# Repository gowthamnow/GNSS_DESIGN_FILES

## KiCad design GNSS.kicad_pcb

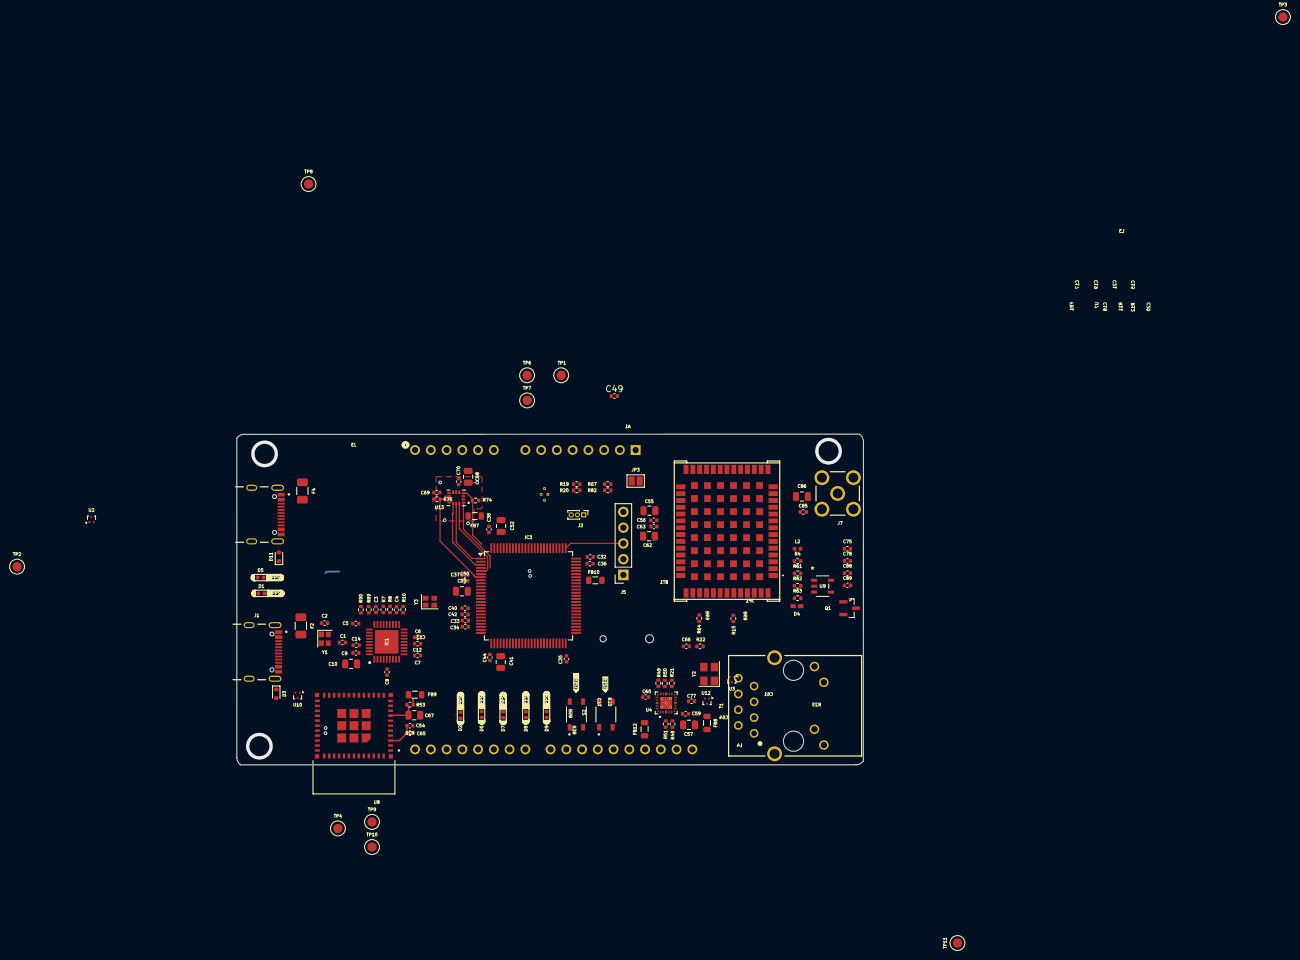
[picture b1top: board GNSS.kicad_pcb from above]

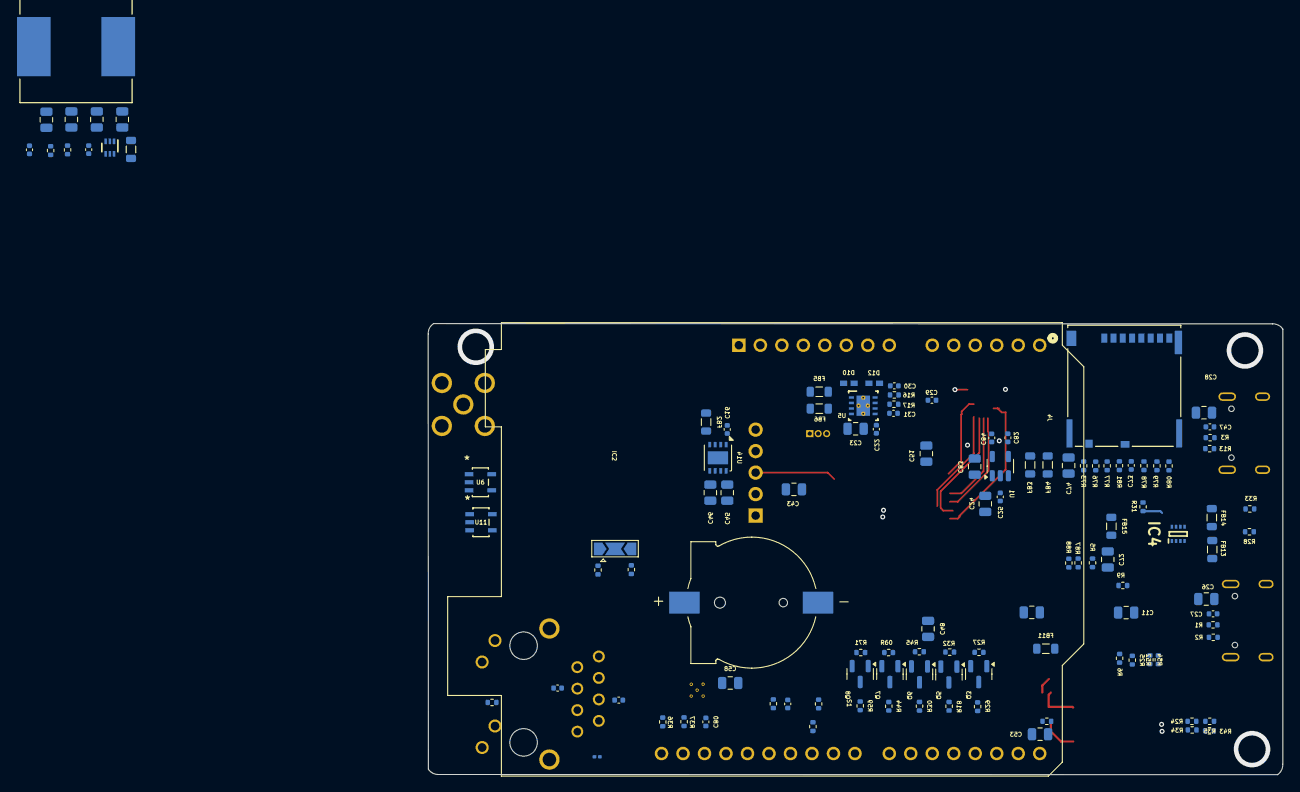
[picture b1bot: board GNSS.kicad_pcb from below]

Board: 4 copper layers, 101.0 x 53.3 mm, 240 parts (116 on the bottom side), 175 nets.

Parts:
A1: Arduino_UNO_R3
BT1: 1056; BAT_1056
C1, C2, C42, C44: 18p; C_0402_1005Metric
C3, C4, C5, C6, C7, C8, C9, C12, C14, C16, C25, C49, C54, C65, C71, C84: 0.1u; C_0402_1005Metric
C10, C23, C43: 4u7; C_0805_2012Metric
C11, C13, C26, C28, C39, C41, C48, C55, C57, C58, C67, C72: 1u; C_0805_2012Metric
C15: 4u7/25V; C_0805_2012Metric
C17, C19, C21: 22u/25V; C_0805_2012Metric
C18, C20: 0.1u/25V; C_0402_1005Metric
C22, C27, C32, C33, C34, C35, C36, C37, C38, C40, C47, C50, C56, C59, C60, C63, C68, C73, C78, C80, C85, C89: 100n; C_0402_1005Metric
C24, C45, C46, C53, C62, C74: 10u; C_0805_2012Metric
C29: 4n7; C_0402_1005Metric
C30, C31: 100p; C_0402_1005Metric
C51, C52: 2.2u; C_0805_2012Metric
C61, C64, C69, C88: 10n; C_0402_1005Metric
C66, C77: 20p; C_0402_1005Metric
C70, C83, C86: 2u2; C_0805_2012Metric
C75: 47p; C_0402_1005Metric
C82: 470p; C_0402_1005Metric
D1, D2, D5, D6, D7, D8, D9: SML-P12U2TT86R; LED_0402_1005Metric
D3, D11: ESD5V0D5-TP; D_SOD-523
D4, D10, D12: PESD0402-140; DIO_PESD0402-140
F2, F4: MF-NSMF150-2; Fuse_1206_3216Metric
FB1, FB2, FB3, FB4, FB5, FB6, FB7, FB8, FB9, FB10, FB11, FB12, FB13, FB14, FB15: FerriteBead; L_0805_2012Metric
IC1: USB2513B_M2; QFN50P600X600X100-37N-D
IC2: ZED-F9P-05B; ZEDF9P05B
IC3: STM32H563VGTx; LQFP-100_14x14mm_P0.5mm
IC4: LM66200DRLR; SOTFL50P160X60-8N
J1, J4: USB4105-GF-A-120; GCT_USB4105-GF-A-120
J2: Conn; PinHeader_1x03_P1.00mm_Vertical
J3: 5033981892; CONN_503398-1892_MOL
J5: Conn_01x05_Pin; PinSocket_1x05_P2.54mm_Vertical
J7: SMA-J-P-X-RA-TH1; SAMTEC_SMA-J-P-X-RA-TH1
JP1: SolderJumper_3_Open; SolderJumper-3_P2.0mm_Open_TrianglePad1.0x1.5mm
JP3: SolderJumper_2_Open; SolderJumper-2_P1.3mm_Open_Pad1.0x1.5mm
L2: LQG15HS47NJ02D; L_0402_1005Metric
L3: SRR1208-120ML; IND_BOURNS_SRR1208
L4: WE-CBF_0603; R_0201_0603Metric
Q1: PMOS; SOT103P240X110-3N
Q3, Q5, Q6, Q7, Q8: BC849; SOT-23
R1, R2, R3, R13: 5K1; R_0402_1005Metric
R4, R5, R7, R12, R63, R87, R88, R89, R90: 100K; R_0402_1005Metric
R6: 12K; R_0402_1005Metric
R8, R9, R10, R15, R25, R26, R27, R31, R32, R35, R38, R43, R45, R48, R51, R52, R53, R54, R58, R60, R64, R67, R68, R69, R70, R71, R73, R74, R75, R76, R77, R78, R79, R80, R81, R82: 10K; R_0402_1005Metric
R11: 450K; R_0402_1005Metric
R16, R17: 60E; R_0402_1005Metric
R18, R28, R29, R30, R33, R44, R59: 560E; R_0402_1005Metric
R19, R20: 0E; R_0402_1005Metric
R21: 6K49; R_0402_1005Metric
R22: 1M; R_0402_1005Metric
R23: 470R; R_0402_1005Metric
R24, R34: 22E; R_0402_1005Metric
R36, R37: 4K7; R_0402_1005Metric
R49, R50: 2K2; R_0402_1005Metric
R61: 30E; R_0402_1005Metric
R62: 1K; R_0402_1005Metric
S1, S2: SKRPABE010; SW_SKRPABE010
T1: WE-RJ45_7499010211A; 7499010211A
TP1, TP2, TP3, TP4, TP6, TP7, TP8, TP9, TP10, TP11: TestPoint; TestPoint_Pad_D2.0mm
U1: MIC5205-3.3YM5; SOT-23-5
U2, U3, U10, U12: TPD2EUSB30A; Texas_DRT-3
U4: DP83825IRMQR; XCVR_DP83825IRMQR
U5: TCAN1042VDRBRQ1; DRB0008F
U6, U11: NC7SZ125M5X; SC-74A_318BQ_ONS
U7: TLV62569ADRLR; DRL0006A
U8: ESP32-C3-MINI-1-N4; XCVR_ESP32-C3-MINI-1-N4
U9: TLV3201AIDBVR; DBV5_TEX
U13: ICM-42688-P; PQFN50P300X250X97-14N
U14: NCV8705ML33TCG; DFN-8-1EP_3x3mm_P0.65mm_EP1.55x2.4mm
Y1, Y3: MURATA_XRCGB24M000FFS1DR0; Crystal_SMD_2016-4Pin_2.0x1.6mm
Y2: ECS-250-18-33-JGN-TR; Crystal_SMD_3225-4Pin_3.2x2.5mm

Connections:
5V: C15.2, C18.2, C19.1, FB1.2, U7.3 (VIN), U7.5 (EN)
+3V3: C17.1, C20.2, C21.1, FB4.1, FB6.1, FB8.1, FB9.1, FB10.1, FB11.1, FB12.1, L3.1, R9.2, R11.2, R36.2, R37.2, R38.2, TP3.1 (1_1)
+3V3_ARDUINO: A1.4 (3V3), FB12.2
+3V3_CAN: FB6.2, U5.5 (VIO)
+3V3_ESP: C53.1, C54.2, C65.2, FB9.2, R25.1, R26.1, R35.2, R43.2, R52.2, R53.2, R54.1, U8.3 (3V3)
+3V3_ETH: C57.1, C58.1, C59.2, C60.2, FB8.2, R48.1, R49.1, R50.1, R51.1, T1.9, U4.6 (VDDA3V3), U4.19 (VDDIO)
+3V3_GNSS: C45.2, C49.2, C55.1, C56.2, C62.1, C63.2, IC2.33 (VCC_1), IC2.34 (VCC_2), IC2.38 (V_USB), R15.1, R30.1, R44.1, R59.1, R64.2, R68.2, U11.5 (VCC), U14.1 (OUT)
+3V3_HUB: C4.2, C5.2, C6.2, C7.2, C8.2, C9.2, C10.2, FB11.2, IC1.5 (VDDA33_1), IC1.10 (VDDA33_2), IC1.15 (VDD33_1), IC1.23 (VDD33_2), IC1.29 (VDDA33_3), IC1.36 (VDDA33_4), R5.2, R8.2, R10.1
+3V3_ICM: C83.2, C84.2, FB7.1, TP8.1 (1_1), U1.5 (OUT)
+3V3_IMU: C68.2, C69.2, C70.1, FB7.2, R74.2, R75.2, U13.5 (VDDIO), U13.8 (VDD)
+3V3_SD: C73.2, C74.1, FB4.2, J3.4, R73.2, R76.2, R77.2, R78.2, R79.2, R80.2, R81.2
/antenna/IN+: R62.1, R63.2, U9.3 (+)
/can/CANH: C30.2, D10.2, J2.1, R16.2, U5.7 (CANH)
/can/CANL: C31.2, D12.1, J2.2, R17.2, U5.6 (CANL)
/controller/BOOT0: IC3.94 (BOOT0), JP3.1 (A), R67.2
/esp/IO8: R54.2, U8.22 (IO8)
/ethernet/XTAL_IN: C77.2, R22.1, U4.13 (XI/50MHZIN), Y2.3 (OUT/IN)
/ethernet/XTAL_OUT: C66.2, R22.2, U4.12 (XO), Y2.1 (IN/OUT)
/usb_hub/CR: C12.2, C13.2, IC1.14 (CRFILT)
/usb_hub/PLL: C11.2, C14.2, IC1.34 (PLLFILT)
/zed_z9p/SAFE_BOOT: IC2.50 (SAFEBOOT_N), JP1.2 (C)
/zed_z9p/V_BCKP: BT1.P, C85.2, C86.1, IC2.36 (V_BCKP)
ANT_DETECT: IC2.4 (ANT_DETECT), U9.1
ANT_FAULT: IC3.39 (PE8), U6.4 (Y)
ANT_OFF: IC2.5 (ANT_OFF_), Q1.2 (G), R4.1, U6.2 (A)
ANT_SHORT_N: C88.2, IC2.6 (ANT_SHORT_N), L2.2, R61.2, U9.4 (-)
ARDUINO_RST_BUT: A1.3 (~RESET), IC3.42 (PE11)
AR_A0: A1.9 (A0), IC3.29 (PA4)
AR_A1: A1.10 (A1), IC3.31 (PA6)
AR_A2: A1.11 (A2), IC3.35 (PB0)
AR_A3: A1.12 (A3), IC3.36 (PB1)
AR_A4: A1.13 (SDA/A4), IC3.15 (PC0)
AR_A5: A1.14 (SCL/A5), IC3.17 (PC2)
AR_D4: A1.19 (D4), IC3.62 (PD15)
AR_D5: A1.20 (D5), IC3.61 (PD14)
AR_D6: A1.21 (D6), IC3.57 (PD10)
AR_D7: A1.22 (D7), IC3.63 (PC6)
AR_D8: A1.23 (D8), IC3.58 (PD11)
AR_D9: A1.24 (D9), IC3.64 (PC7)
AR_MISO: A1.27 (D12), IC3.53 (PB14)
AR_MOSI: A1.26 (D11), IC3.18 (PC3)
AR_RX: A1.16 (D1/TX), IC3.56 (PD9)
AR_SCK: A1.28 (D13), IC3.52 (PB13)
AR_SCL: A1.32 (SCL/A5), IC3.92 (PB6), R36.1, TP7.1 (1_1)
AR_SDA: A1.31 (SDA/A4), IC3.93 (PB7), R37.1, TP6.1 (1_1)
AR_SS: A1.25 (D10), IC3.26 (PA3), R38.1
AR_TX: A1.15 (D0/RX), IC3.55 (PD8)
CAN_RXD: IC3.81 (PD0), U5.4 (RXD)
CAN_STB: IC3.88 (PD7), U5.8 (STB)
CAN_TXD: IC3.82 (PD1), U5.1 (TXD)
ESP_BOOT: IC3.46 (PE15), R52.1, TP4.1 (1_1), U8.23 (IO9)
ESP_D_N: IC1.3 (USBDM_DN2/PRT_DIS_M2), U8.26 (IO18), U10.2 (D-)
ESP_D_P: IC1.4 (USBDP_DN2/PRT_DIS_P2), U8.27 (IO19), U10.1 (D+)
ESP_EN: C67.1, IC3.45 (PE14), R53.1, U8.8 (EN)
ESP_INT: IC3.44 (PE13), R25.2, U8.18 (IO4)
ESP_RXD: IC3.69 (PA10), R34.1, R43.1, TP10.1 (1_1)
ESP_TXD: IC3.68 (PA9), R24.1, R35.1, TP9.1 (1_1)
ETH_CRS_DV: IC3.32 (PA7), U4.20 (CRS_DV/S(PHYADD1))
ETH_INTR: IC3.23 (PA0), R51.2, U4.3 (INTR/PWRDN)
ETH_MDC: IC3.16 (PC1), R49.2, U4.16 (MDC)
ETH_MDIO: IC3.25 (PA2), R50.2, U4.15 (MDIO)
ETH_REFCLK: IC3.24 (PA1), U4.2 (50MHZOUT/LED2/S(RX_DV_EN))
ETH_RST_N: IC3.38 (PE7), R48.2, U4.5 (~RST)
ETH_RX_D0_N: IC3.33 (PC4), U4.18 (RX_D0/S(PHYADD0))
ETH_RX_D1_N: IC3.34 (PC5), U4.17 (RX_D1/S(MASTER/SLAVE))
ETH_TX_D0_P: IC3.51 (PB12), U4.23 (TX_D0)
ETH_TX_D1_P: IC3.54 (PB15), U4.24 (TX_D1)
ETH_TX_EN: IC3.30 (PA5), U4.1 (TX_EN)
EX_VBUS: C28.1, C47.2, F4.1, FB14.1, IC4.6 (VIN2), R28.1
GEOFENCE: IC2.19 (GEOFENCE_STAT), R71.2
GND: A1.6 (GND), A1.7 (GND), A1.29 (GND), BT1.N, C1.2, C2.2, C3.1, C4.1, C5.1, C6.1, C7.1, C8.1, C9.1, C10.1, C11.1, C12.1, C13.1, C14.1, C15.1, C16.1, C17.2, C18.1, C19.2, C20.1, C21.2, C22.1, C23.2, C24.1, C25.1, C26.2, C27.1, C28.2, C29.1, C30.1, C31.1, C32.1, C33.1, C34.1, C35.1, C36.1, C37.1, C38.1, C39.2, C40.1, C41.2, C42.2, C43.2, C44.2, C45.1, C46.1, C47.1, C48.2, C49.1, C50.1, C51.2, C52.2, C53.2, C54.1, C55.2, C56.1, C57.2, C58.2, C59.1, C60.1, C61.1, C62.2, C63.1, C64.1, C65.1, C66.1, C67.2, C68.1, C69.1, C70.2, C71.1, C72.1, C73.1, C74.2, C77.1, C78.1, C80.1, C82.1, C83.1, C84.1, C85.1, C86.2, C88.1, C89.1, D1.1, D3.2 (A), D4.1, D5.1, D10.1, D11.2 (A), D12.2, IC1.11 (TEST), IC1.37 (GND), IC2.1 (GND_1), IC2.3 (GND_2), IC2.12 (GND_3), IC2.14 (GND_4), IC2.32 (GND_5), IC2.37 (GND_6), IC2.41 (GND_7), IC2.47 (D_SEL), IC2.48 (GND_8), IC2.55 (GND_9), IC2.56 (GND_10), IC2.57 (GND_11), IC2.58 (GND_12), IC2.59 (GND_13), IC2.60 (GND_14), IC2.61 (GND_15), IC2.62 (GND_16), IC2.63 (GND_17), IC2.64 (GND_18), IC2.65 (GND_19), IC2.66 (GND_20), IC2.67 (GND_21), IC2.68 (GND_22), IC2.69 (GND_23), IC2.70 (GND_24), IC2.71 (GND_25), IC2.72 (GND_26), IC2.73 (GND_27), IC2.74 (GND_28), IC2.75 (GND_29), IC2.76 (GND_30), IC2.77 (GND_31), IC2.78 (GND_32), IC2.79 (GND_33), IC2.80 (GND_34), IC2.81 (GND_35), IC2.82 (GND_36), IC2.83 (GND_37), IC2.84 (GND_38), IC2.85 (GND_39), IC2.86 (GND_40), IC2.87 (GND_41), IC2.88 (GND_42), IC2.89 (GND_43), IC2.90 (GND_44), IC2.91 (GND_45), IC2.92 (GND_46), IC2.93 (GND_47), IC2.94 (GND_48), IC2.95 (GND_49), IC2.96 (GND_50), IC2.97 (GND_51), IC2.98 (GND_52), IC2.99 (GND_53), IC2.100 (GND_54), IC2.101 (GND_55), IC2.102 (GND_56), IC3.10 (VSS), IC3.19 (VSSA), IC3.20 (VREF-), IC3.27 (VSS), IC3.49 (VSS), IC3.74 (VSS), IC3.99 (VSS), IC4.1 (GND@1), IC4.4 (ON), IC4.5 (GND@2), J1.A1_B12 (GND), J1.B1_A12 (GND), J1.SH1 (SHELL_GND), J1.SH2 (SHELL_GND), J1.SH3 (SHELL_GND), J1.SH4 (SHELL_GND), J2.3, J3.6, J3.9, J4.A1_B12 (GND), J4.B1_A12 (GND), J4.SH1 (SHELL_GND), J4.SH2 (SHELL_GND), J4.SH3 (SHELL_GND), J4.SH4 (SHELL_GND), J5.5, J7.2, J7.3, J7.4, J7.5, L4.2, Q3.2 (E), Q5.2 (E), Q6.2 (E), Q7.2 (E), Q8.2 (E), R1.1, R2.1, R3.1, R6.1, R7.2, R12.1, R13.1, R21.1, R63.1, R69.2, R82.2, R87.1, R88.1, R90.2, S1.3, S1.4, S2.3, S2.4, TP2.1 (1_1), U1.2 (GND), U2.3 (GND), U3.3 (GND), U4.9 (GND), U4.21 (GND), U4.25 (EXP), U4.26 (EXP), U4.27 (EXP), U4.28 (EXP), U4.29 (EXP), U4.30 (EXP), U5.2 (GND), U5.9 (PAD), U6.1 (*OE), U6.3 (GND), U7.2 (GND), U8.1 (GND), U8.2 (GND), U8.11 (GND), U8.14 (GND), U8.36 (GND), U8.37 (GND), U8.38 (GND), U8.39 (GND), U8.40 (GND), U8.41 (GND), U8.42 (GND), U8.43 (GND), U8.44 (GND), U8.45 (GND), U8.46 (GND), U8.47 (GND), U8.48 (GND), U8.49_1 (GND), U8.49_2 (GND), U8.49_3 (GND), U8.49_4 (GND), U8.49_5 (GND), U8.49_6 (GND), U8.49_7 (GND), U8.49_8 (GND), U8.49_9 (GND), U8.50 (GND), U8.51 (GND), U8.52 (GND), U8.53 (GND), U9.2 (V-), U10.3 (GND), U11.1 (*OE), U11.3 (GND), U12.3 (GND), U13.6 (GND), U14.4 (GND), U14.9 (EXP), Y2.2 (GND), Y2.4 (GND)
GNSS_D_N: IC1.6 (USBDM_DN3/PRT_DIS_M3), IC2.39 (USB_DM), U3.2 (D-)
GNSS_D_P: IC1.7 (USBDP_DN3/PRT_DIS_P3), IC2.40 (USB_DP), U3.1 (D+)
GN_CS: IC2.44 (SDA_/_SPI_CS_N), IC3.77 (PA15(JTDI)), R64.1
GN_EXINT: IC2.51 (EXTINT), IC3.96 (PB9)
GN_LED: IC3.84 (PD3), R32.2
GN_MISO: IC2.42 (TXD_/_SPI_SDO), IC3.90 (PB4(NJTRST))
GN_MOSI: IC2.43 (RXD_/_SPI_SDI), IC3.87 (PD6)
GN_SCK: IC2.45 (SCL_/_SPI_CLK), IC3.89 (PB3(JTDO)
GN_TIMEPULSE: IC2.53 (TIMEPULSE), IC3.91 (PB5), U11.2 (A)
IMU_CS: IC3.3 (PE4), U13.12 (AP_CS)
IMU_MISO: IC3.4 (PE5), U13.1 (AP_SDO/AP_AD0)
IMU_MOSI: IC3.5 (PE6), U13.14 (AP_SDA/AP_SDIO/AP_SDI)
IMU_SCK: IC3.1 (PE2), U13.13 (AP_SCL/AP_SCLK)
INT1_ACCEL: IC3.2 (PE3), R74.1, U13.4 (INT1/INT)
INT1_GYRO: IC3.7 (PC13), R75.1, U13.9 (INT2/FSYNC/CLKIN)
JTCK/SWCLK: A1.17 (D2), IC3.76 (PA14(JTCK), J5.3
JTMS/SWDIO: A1.18 (D3), IC3.72 (PA13(JTMS), J5.4
LED_LINK: R23.1, U4.4 (LED0/S(ANEG_DIS))
unnamed: A1.30 (AREF), C80.2
unnamed: C29.2, R16.1, R17.1
unnamed: C51.1, C52.1, IC3.48 (VCAP), IC3.98 (VCAP)
unnamed: C75.2, L2.1
unnamed: D1.2, R28.2
unnamed: D2.2, R18.2
unnamed: D5.2, R33.2
unnamed: D6.2, R29.2
unnamed: D7.2, R30.2
unnamed: D8.2, R44.2
unnamed: D9.2, R59.2
unnamed: IC1.25 (HS_IND/CFG_SEL1), R7.1
unnamed: IC1.35 (RBIAS), R6.2
unnamed: IC1.28 (SUSP_IND/LOCAL_PWR/NON_REM0), R9.1
unnamed: IC1.27 (VBUS_DET), R89.1, R90.1
unnamed: C1.1, IC1.33 (XTALIN/CLKIN), Y1.3
unnamed: C2.1, IC1.32 (XTALOUT), Y1.1
unnamed: C42.1, IC3.12 (PH0), Y3.1
unnamed: C44.1, IC3.13 (PH1), Y3.3
unnamed: IC4.8 (ST), R31.1, TP1.1 (1_1)
unnamed: J1.A5 (CC1), R1.2
unnamed: J1.B5 (CC2), R2.2
unnamed: J4.A5 (CC1), R3.2
unnamed: J4.B5 (CC2), R13.2
unnamed: JP1.1 (A), R68.1
unnamed: JP1.3 (B), R69.1
unnamed: JP3.2 (B), R82.1
unnamed: Q1.1 (D), R61.1, R62.2
unnamed: Q3.1 (B), R27.1
unnamed: D2.1, Q3.3 (C)
unnamed: Q5.1 (B), R32.1
unnamed: D6.1, Q5.3 (C)
unnamed: Q6.1 (B), R45.1
unnamed: D7.1, Q6.3 (C)
unnamed: Q7.1 (B), R60.1
unnamed: D8.1, Q7.3 (C)
unnamed: Q8.1 (B), R71.1
unnamed: D9.1, Q8.3 (C)
unnamed: R23.2, T1.10
unnamed: C61.2, T1.5 (CRD)
unnamed: C64.2, T1.4 (CTD)
unnamed: T1.3 (RD+), U4.8 (RD_P)
unnamed: T1.6 (RD-), U4.7 (RD_M)
unnamed: L4.1, T1.8, T1.S1 (SHIELD1), T1.S2 (SHIELD2)
unnamed: T1.1 (TD+), U4.11 (TD_P)
unnamed: T1.2 (TD-), U4.10 (TD_M)
unnamed: C82.2, U1.4 (BP)
unnamed: R21.2, U4.14 (RBIAS)
unnamed: R11.1, R12.2, U7.1 (FB)
unnamed: L3.2, U7.4 (SW)
unnamed: R26.2, U8.5 (IO2)
unnamed: R24.2, U8.30 (RXD0)
unnamed: R34.2, U8.31 (TXD0)
PG_VBUS: C26.1, C27.2, C72.2, F2.1, FB13.1, IC4.3 (VIN1), R31.2, R33.1, R89.2
RESET_GNSS: IC2.49 (RESET_N), IC3.97 (PE0), R15.2
RF_IN: C75.1, D4.2, IC2.2 (RF_IN), J7.1
RF_VCC: C78.2, C89.2, IC2.7 (VCC_RF), Q1.3 (S), R4.2, U6.5 (VCC), U9.5 (V+)
RST_BUT: C71.2, IC3.14 (NRST), J5.2, R70.1, S2.1, S2.2
RTK_STAT: IC2.20 (RTK_STAT), R60.2
SD_CLK: IC3.80 (PC12), J3.5, R78.1
SD_CMD: IC3.37 (PB2), J3.3, R77.1
SD_DAT0: IC3.65 (PC8), J3.7, R79.1
SD_DAT1: IC3.66 (PC9), J3.8, R80.1
SD_DAT2: IC3.78 (PC10), J3.1, R73.1
SD_DAT3: IC3.79 (PC11), J3.2, R76.1
SD_DETECT: IC3.67 (PA8), J3.10, R81.1
STM_3V3: C32.2, C33.2, C34.2, C35.2, C36.2, C37.2, C38.2, C43.1, C48.1, FB10.2, IC3.6 (VBAT), IC3.11 (VDD), IC3.28 (VDD), IC3.50 (VDD), IC3.73 (VDDUSB), IC3.75 (VDD), IC3.100 (VDD), J5.1, R18.1, R19.1, R29.1, R58.2, R67.1, R70.2
STM_D_N: IC1.1 (USBDM_DN1/PRT_DIS_M1), IC3.70 (PA11), U12.2 (D-)
STM_D_P: IC1.2 (USBDP_DN1/PRT_DIS_P1), IC3.71 (PA12), U12.1 (D+)
TIMEPULSE_LED: R45.2, U11.4 (Y)
TX_READY: IC2.46 (TX_READY), IC3.95 (PB8)
USB_N: IC1.30 (USBDM_UP), J1.A7 (DN1), J1.B7 (DN2)
USB_P: IC1.31 (USBDP_UP), J1.A6 (DP1), J1.B6 (DP2)
USB_RST: C3.2, IC1.26 (RESET_N), IC3.41 (PE10), R5.1
USB_SCL: IC1.24 (SCL/SMBCLK/CFG_SEL0), IC3.59 (PD12), R8.1, R87.2
USB_SDA: IC1.22 (SDA/SMBDATA/NON_REM1), IC3.60 (PD13), R10.2, R88.2
USER_BUT: IC3.85 (PD4), R58.1, S1.1, S1.2
USER_LED: IC3.86 (PD5), R27.2
VBUS: D3.1 (K), D11.1 (K), F2.2, F4.2, J1.A4_B9 (VBUS), J1.B4_A9 (VBUS), J4.A4_B9 (VBUS), J4.B4_A9 (VBUS)
VDDA: C39.1, C40.2, IC3.22 (VDDA), R19.2, R20.2
VIN: A1.5 (+5V), FB1.1, FB2.1, FB3.1, FB5.1, FB13.2, FB14.2, FB15.2
VIN_CAN: C22.2, C23.1, FB5.2, U5.3 (VCC)
VIN_GNSS: C16.2, C46.2, FB2.2, TP11.1 (1_1), U14.5 (EN), U14.8 (IN)
VIN_ICM: C24.2, C25.2, FB3.2, U1.1 (IN), U1.3 (EN)
VOUT_MUX: FB15.1, IC4.2 (VOUT@1), IC4.7 (VOUT@2)
VREFP: C41.1, C50.2, IC3.21 (VREF+), R20.1

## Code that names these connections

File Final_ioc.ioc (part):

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Mcu.Name=STM32H563VGTx
Mcu.Package=LQFP100
Mcu.UserName=STM32H563VGTx
PA0.Signal=S_TIM2_CH1
PA1.GPIOParameters=GPIO_Label
PA1.GPIO_Label=ARDUINO_A4
PA1.Signal=ADCx_INP1
PA11.GPIOParameters=GPIO_Label
PA11.GPIO_Label=USB_OTG_HS_DM
PA11.Mode=Device
PA11.Signal=USB_DM
PA12.GPIOParameters=GPIO_Label
PA12.GPIO_Label=USB_OTG_HS_DP
PA12.Mode=Device
PA12.Signal=USB_DP
PA13(JTMS/SWDIO).Signal=DEBUG_JTMS-SWDIO
PA14(JTCK/SWCLK).Signal=DEBUG_JTCK-SWCLK
PA15(JTDI).GPIOParameters=GPIO_Label
PA15(JTDI).GPIO_Label=ARDUINO_CS
PA15(JTDI).Mode=NSS_Signal_Hard_Output
PA15(JTDI).Signal=SPI3_NSS
PA2.GPIOParameters=GPIO_Label
PA2.GPIO_Label=ARDUINO_A5
PA2.Signal=ADCx_INP14
PA4.GPIOParameters=GPIO_Label
PA4.GPIO_Label=GNSS_CS
PA4.Mode=NSS_Signal_Hard_Output
PA4.Signal=SPI1_NSS
PA5.GPIOParameters=GPIO_Label
PA5.GPIO_Label=GNSS_SCK
PA5.Mode=Full_Duplex_Master
PA5.Signal=SPI1_SCK
PA6.GPIOParameters=GPIO_Label
PA6.GPIO_Label=GNSS_MISO
PA6.Mode=Full_Duplex_Master
PA6.Signal=SPI1_MISO
PA7.GPIOParameters=GPIO_Label
PA7.GPIO_Label=GNSS_MOSI
PA7.Mode=Full_Duplex_Master
PA7.Signal=SPI1_MOSI
PB0.GPIOParameters=GPIO_Label
PB0.GPIO_Label=GNSS_RST
PB0.Signal=GPIO_Output
PB1.GPIOParameters=GPIO_Label
PB1.GPIO_Label=GNSS_EXT_INT
PB1.Signal=GPXTI1
PB10.GPIOParameters=GPIO_Label
PB10.GPIO_Label=ESP_BOOT
PB10.Signal=GPIO_Output
PB14.GPIOParameters=GPIO_Label
PB14.GPIO_Label=ESP_UART_TX
PB14.Mode=Asynchronous
PB14.Signal=USART1_TX
PB15.GPIOParameters=GPIO_Label
PB15.GPIO_Label=ESP_UART_RX
PB15.Mode=Asynchronous
PB15.Signal=USART1_RX
PB3(JTDO/TRACESWO).GPIOParameters=GPIO_Label
PB3(JTDO/TRACESWO).GPIO_Label=ARDUINO_SCK
PB3(JTDO/TRACESWO).Mode=Full_Duplex_Master
PB3(JTDO/TRACESWO).Signal=SPI3_SCK
PB4(NJTRST).GPIOParameters=GPIO_Label
PB4(NJTRST).GPIO_Label=ARDUINO_MISO
PB4(NJTRST).Mode=Full_Duplex_Master
PB4(NJTRST).Signal=SPI3_MISO
PB6.GPIOParameters=GPIO_Label
PB6.GPIO_Label=ARDUINO_SCL
PB6.Mode=I2C
PB6.Signal=I2C1_SCL
PB7.GPIOParameters=GPIO_Label
PB7.GPIO_Label=ARDUINO_SDA
PB7.Mode=I2C
PB7.Signal=I2C1_SDA
PC0.GPIOParameters=GPIO_Label
PC0.GPIO_Label=ARDUINO_A0
PC0.Signal=ADCx_INP10
PC1.GPIOParameters=GPIO_Label
PC1.GPIO_Label=ARDUINO_A1
PC1.Signal=ADCx_INP11
PC10.Mode=mmc_4_bits_Wide_bus
PC10.Signal=SDMMC1_D2
PC11.Mode=mmc_4_bits_Wide_bus
PC11.Signal=SDMMC1_D3
PC12.Mode=mmc_4_bits_Wide_bus
PC12.Signal=SDMMC1_CK
PC13.GPIOParameters=GPIO_Label
PC13.GPIO_Label=IMU_ACC_2
PC13.Signal=GPIO_Input
PC14-OSC32_IN(OSC32_IN).GPIOParameters=GPIO_Label
PC14-OSC32_IN(OSC32_IN).GPIO_Label=IMU_GYRO_1
PC14-OSC32_IN(OSC32_IN).Signal=GPIO_Input
PC15-OSC32_OUT(OSC32_OUT).GPIOParameters=GPIO_Label
PC15-OSC32_OUT(OSC32_OUT).GPIO_Label=IMU_GYRO_2
PC15-OSC32_OUT(OSC32_OUT).Signal=GPIO_Input
PC2.GPIOParameters=GPIO_Label
PC2.GPIO_Label=ARDUINO_A2
PC2.Signal=ADCx_INP12
PC3.GPIOParameters=GPIO_Label
PC3.GPIO_Label=ARDUINO_A3
PC3.Signal=ADCx_INP13
PC5.GPIOParameters=GPIO_Label
PC5.GPIO_Label=GNSS_TX_READY
PC5.Signal=GPIO_Output
PC6.GPIOParameters=GPIO_Label
PC6.GPIO_Label=ARDUINO_D3
PC6.Signal=GPIO_Output
PC7.GPIOParameters=GPIO_Label
PC7.GPIO_Label=ARDUINO_D2
PC7.Signal=GPIO_Output
PC8.Mode=mmc_4_bits_Wide_bus
PC8.Signal=SDMMC1_D0
PC9.Mode=mmc_4_bits_Wide_bus
PC9.Signal=SDMMC1_D1
PD0.Mode=FDCAN_Activate
PD0.Signal=FDCAN1_RX
PD1.Mode=FDCAN_Activate
PD1.Signal=FDCAN1_TX
PD10.GPIOParameters=GPIO_Label
PD10.GPIO_Label=ARDUINO_D9
PD10.Signal=GPIO_Output
PD11.GPIOParameters=GPIO_Label
PD11.GPIO_Label=ARDUINO_D8
PD11.Signal=GPIO_Output
PD12.GPIOParameters=GPIO_Label
PD12.GPIO_Label=ARDUINO_D7
PD12.Signal=GPIO_Output
PD13.GPIOParameters=GPIO_Label
PD13.GPIO_Label=ARDUINO_D6
PD13.Signal=GPIO_Output
PD14.GPIOParameters=GPIO_Label
PD14.GPIO_Label=ARDUINO_D5
PD14.Signal=GPIO_Output
PD15.GPIOParameters=GPIO_Label
PD15.GPIO_Label=ARDUINO_D4
PD15.Signal=GPIO_Output
PD2.Mode=mmc_4_bits_Wide_bus
PD2.Signal=SDMMC1_CMD
PD3.GPIOParameters=GPIO_Label
PD3.GPIO_Label=GNSS_LED
PD3.Signal=GPIO_Output
PD4.GPIOParameters=GPIO_Label
PD4.GPIO_Label=USER_BUTTON
PD4.Signal=GPIO_Output
PD5.GPIOParameters=GPIO_Label
PD5.GPIO_Label=USER_LED
PD5.Signal=GPIO_Output
PD6.GPIOParameters=GPIO_Label
PD6.GPIO_Label=ARDIUNO_MOSI
PD6.Mode=Full_Duplex_Master
PD6.Signal=SPI3_MOSI
PD7.GPIOParameters=GPIO_Label
PD7.GPIO_Label=FD_STD
PD7.Signal=GPIO_Output
PD8.GPIOParameters=GPIO_Label
PD8.GPIO_Label=ARDUINO_TX
PD8.Mode=Asynchronous
PD8.Signal=USART3_TX
PD9.GPIOParameters=GPIO_Label
PD9.GPIO_Label=ARDUINO_RX
PD9.Mode=Asynchronous
PD9.Signal=USART3_RX
PE13.GPIOParameters=GPIO_Label
PE13.GPIO_Label=ESP_INT
PE13.Signal=GPIO_Output
PE14.GPIOParameters=GPIO_Label
PE14.GPIO_Label=ESP1_EN
PE14.Signal=GPIO_Output
PE15.GPIOParameters=GPIO_Label
PE15.GPIO_Label=ESP_RST
PE15.Signal=GPIO_Output
PE2.GPIOParameters=GPIO_Label
PE2.GPIO_Label=IMU_SCK
PE2.Mode=Full_Duplex_Master
PE2.Signal=SPI4_SCK
PE3.GPIOParameters=GPIO_Label
PE3.GPIO_Label=IMU_ACC_1
PE3.Signal=GPIO_Input
PE4.GPIOParameters=GPIO_Label
PE4.GPIO_Label=IMU_CS_1
PE4.Mode=NSS_Signal_Hard_Output
PE4.Signal=SPI4_NSS
PE5.GPIOParameters=GPIO_Label
PE5.GPIO_Label=IMU_MISO
PE5.Mode=Full_Duplex_Master
PE5.Signal=SPI4_MISO
PE6.GPIOParameters=GPIO_Label
PE6.GPIO_Label=IMU_MOSI
PE6.Mode=Full_Duplex_Master
PE6.Signal=SPI4_MOSI
PH0-OSC_IN(PH0).Mode=HSE-External-Oscillator
PH0-OSC_IN(PH0).Signal=RCC_OSC_IN
PH1-OSC_OUT(PH1).Mode=HSE-External-Oscillator
PH1-OSC_OUT(PH1).Signal=RCC_OSC_OUT
RCC.HSE_VALUE=25000000
RCC.SYSCLKFreq_VALUE=32000000
board=custom
